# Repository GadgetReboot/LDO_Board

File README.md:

# LDO_Board
LDO 5v and 8v distribution pcb to provide logic and motor power for up to 4 fader slide pots

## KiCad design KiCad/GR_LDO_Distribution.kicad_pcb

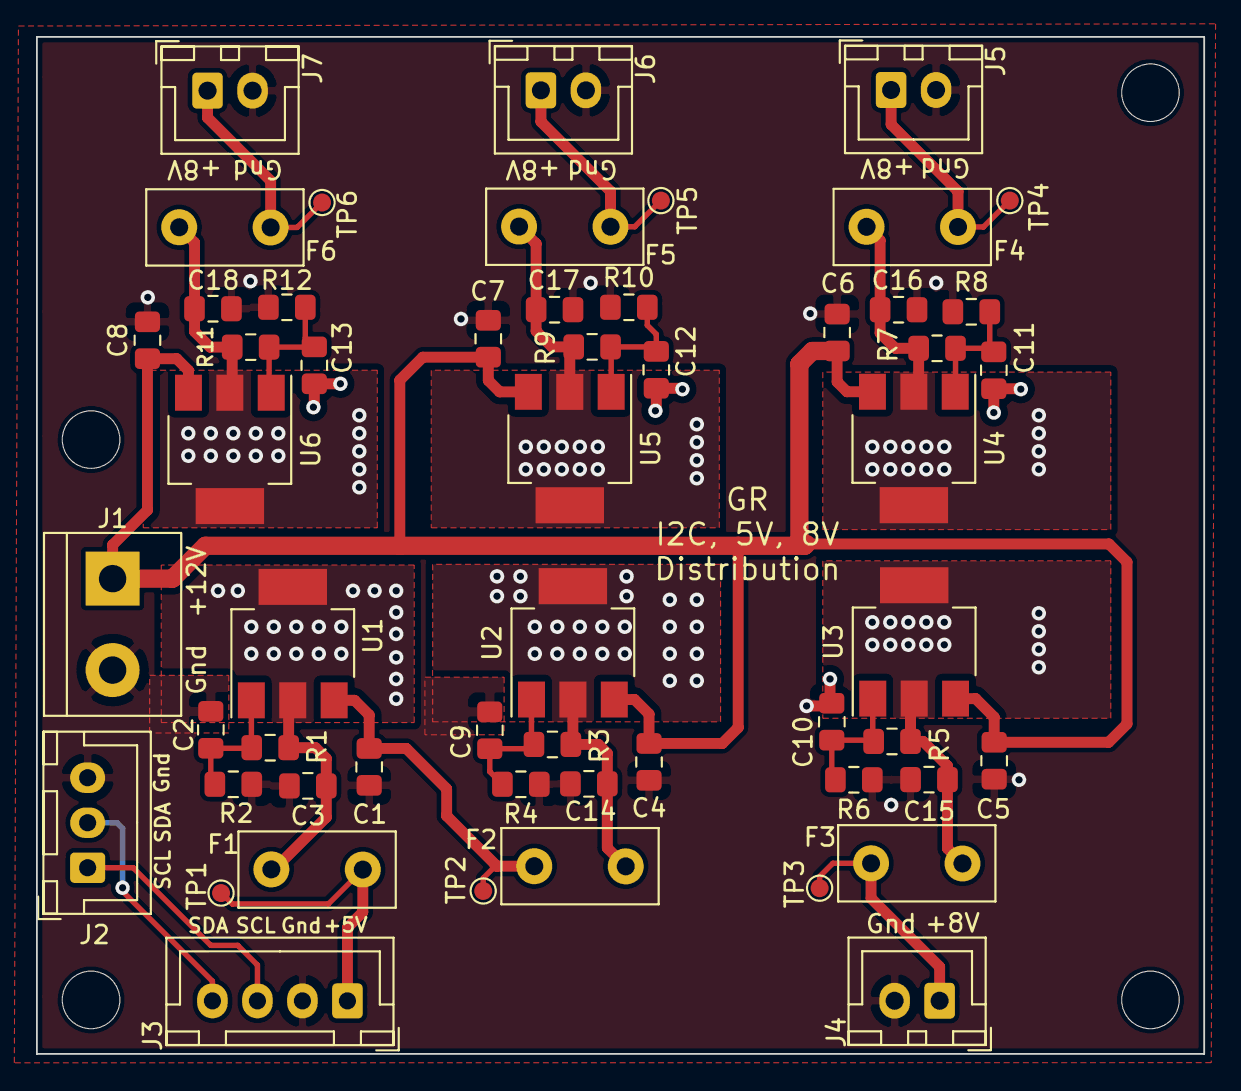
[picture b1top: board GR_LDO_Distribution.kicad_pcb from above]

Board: 2 copper layers, 64.8 x 56.5 mm, 59 parts (0 on the bottom side), 22 nets.

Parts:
C1, C3, C4, C5, C6, C7, C8, C14, C15, C16, C17, C18: 10uF; C_0805_2012Metric_Pad1.15x1.40mm_HandSolder
C2, C9, C10, C11, C12, C13: DNI; C_0805_2012Metric_Pad1.15x1.40mm_HandSolder
F1, F2, F3, F4, F5, F6: JK60-090; Fuse_Littelfuse_395Series
J1: Screw_Terminal_01x02; TerminalBlock_bornier-2_P5.08mm
J2: Conn_01x03; JST_XH_B3B-XH-A_1x03_P2.50mm_Vertical
J3: Conn_01x04; JST_XH_B4B-XH-A_1x04_P2.50mm_Vertical
J4, J5, J6, J7: Conn_01x02; JST_XH_B2B-XH-A_1x02_P2.50mm_Vertical
MH1, MH2, MH3, MH4: MountingHole; MountingHole_3.2mm_M3
R1: 300r; R_0805_2012Metric_Pad1.15x1.40mm_HandSolder
R2: 910r; R_0805_2012Metric_Pad1.15x1.40mm_HandSolder
R3, R5, R7, R9, R11: 220r; R_0805_2012Metric_Pad1.15x1.40mm_HandSolder
R4, R6, R8, R10, R12: 1K2; R_0805_2012Metric_Pad1.15x1.40mm_HandSolder
TP1, TP2, TP3, TP4, TP5, TP6: TestPoint; TestPoint_Pad_D1.0mm
U1, U2, U3, U4, U5, U6: AMS1117; SOT-223-3_TabPin2

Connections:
/5VIn: C1.1, F2.1, TP2.1, U1.3
/SCL: J2.1, J3.3
/SDA: J2.2, J3.4
/Vin: C4.1, C5.1, C6.1, C7.1, C8.1, J1.1, U2.3, U3.3, U4.3, U5.3, U6.3
GNDREF: C1.2, C2.2, C3.2, C4.2, C5.2, C6.2, C7.2, C8.2, C9.2, C10.2, C11.2, C12.2, C13.2, C14.2, C15.2, C16.2, C17.2, C18.2, J1.2, J2.3, J3.2, J4.2, J5.2, J6.2, J7.2, R2.1, R4.1, R6.1, R8.1, R10.1, R12.1
unnamed: C2.1, R1.1, R2.2, U1.1
unnamed: C3.1, F1.2, R1.2, U1.2
unnamed: C9.1, R3.1, R4.2, U2.1
unnamed: C10.1, R5.1, R6.2, U3.1
unnamed: C11.1, R7.1, R8.2, U4.1
unnamed: C12.1, R9.1, R10.2, U5.1
unnamed: C13.1, R11.1, R12.2, U6.1
unnamed: C14.1, F2.2, R3.2, U2.2
unnamed: C15.1, F3.2, R5.2, U3.2
unnamed: C16.1, F4.2, R7.2, U4.2
unnamed: C17.1, F5.2, R9.2, U5.2
unnamed: C18.1, F6.2, R11.2, U6.2
unnamed: F1.1, J3.1, TP1.1
unnamed: F3.1, J4.1, TP3.1
unnamed: F4.1, J5.1, TP4.1
unnamed: F5.1, J6.1, TP5.1
unnamed: F6.1, J7.1, TP6.1
